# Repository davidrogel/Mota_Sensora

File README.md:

# Proyecto Mota Sensora

Proyecto para la creación de una Mota Sensora que permita leer los sensores acoplados.

### Dependencias ⚠️⚠️⚠️

La Mota depende del módulo que lee el sensor DHT11. Para descargar el proyecto junto a las dependencias usar:

```
git clone --recurse-submodules https://github.com/davidrogel/Mota_Sensora
```

## Sensores

| Sensor | Documentación |
|---|---|
| DHT11 | [Enlace](https://www.mouser.com/datasheet/2/758/DHT11-Technical-Data-Sheet-Translated-Version-1143054.pdf) |
| MQ-2 | [Enlace](http://gas-sensor.ru/pdf/combustible-gas-sensor.pdf) |
| MQ-3 | [Enlace](https://www.sparkfun.com/datasheets/Sensors/MQ-3.pdf) |

## Microcontrolador - ESP32

### Proyecto Base y otros

Se ha usado el proyecto de ejemplo **[ESP HTTP Client Example](https://github.com/espressif/esp-idf/tree/master/examples/protocols/esp_http_client)** como base para la creación del proyecto actual ya que ayuda a la hora de poder conectarse a una Wifi y trae ejemplos útiles de envio de datos a traves del protocolo HTTP.

A parte del proyecto mencionado antes, se ha usado el proyecto de ejemplo **[adc](https://github.com/espressif/esp-idf/tree/master/examples/peripherals/adc/single_read/adc)** para la lectura de valores analógicos

### Configuración y uso

Dentro de la carpeta del proyecto, configurar el tipo de dispositivo y abrir el **menuconfig** para configurar la ssid y password del WiFi y la api-key de thingspeak. También es posible modificar el pin digital del sensor DHT11.
```
idf.py set-target esp32
idf.py menuconfig
```

Tras configurar, hacer build y flashear el programa
```
idf.py build
idf.py -p PORT flash
```

El parámetro **PORT** será el USB que tengais conectado al dispositivo, en linux se puede hacer lo siguiente para buscar el USB:
```
ls /dev/ttyUSB*
```

Por último podeis monitorizar lo que está pasando (obtener los datos de salida por consola) usando monitor:
```
idf.py -p PORT monitor
```

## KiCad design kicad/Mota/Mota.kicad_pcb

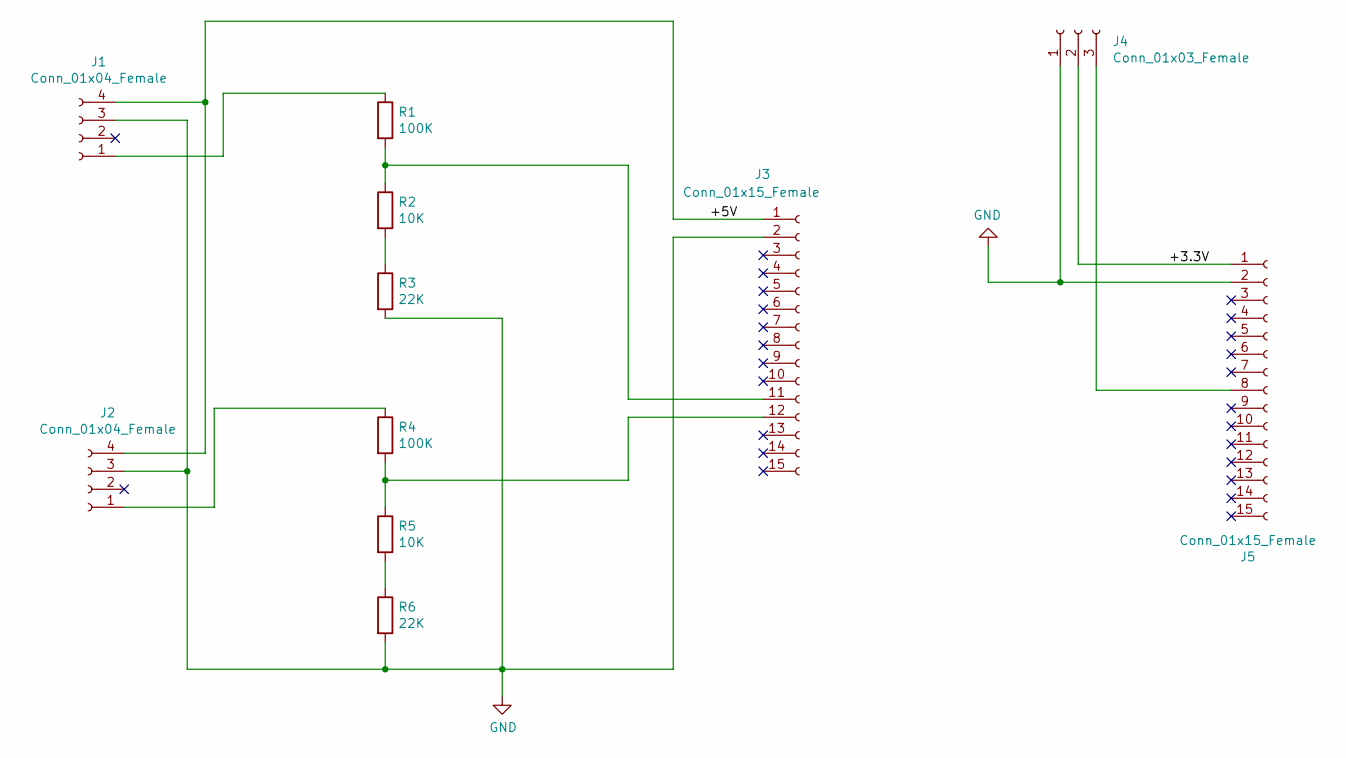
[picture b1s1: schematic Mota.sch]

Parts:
J1, J2: Conn_01x04_Female; PinSocket_1x04_P2.54mm_Vertical
J3, J5: Conn_01x15_Female; PinSocket_1x15_P2.54mm_Vertical
J4: Conn_01x03_Female; PinSocket_1x03_P2.54mm_Vertical
R1, R4: 100K; R_Axial_DIN0207_L6.3mm_D2.5mm_P2.54mm_Vertical
R2, R5: 10K; R_Axial_DIN0207_L6.3mm_D2.5mm_P2.54mm_Vertical
R3, R6: 22K; R_Axial_DIN0207_L6.3mm_D2.5mm_P2.54mm_Vertical

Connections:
/+3.3V: J4.2, J5.1
/+5V: J1.4, J2.4, J3.1
GND: J1.3, J2.3, J3.2, J4.1, J5.2, R3.2, R6.2
unnamed: J1.1, R1.1
unnamed: J2.1, R4.1
unnamed: J3.11, R1.2, R2.1
unnamed: J3.12, R4.2, R5.1
unnamed: J4.3, J5.8
unnamed: R2.2, R3.1
unnamed: R5.2, R6.1

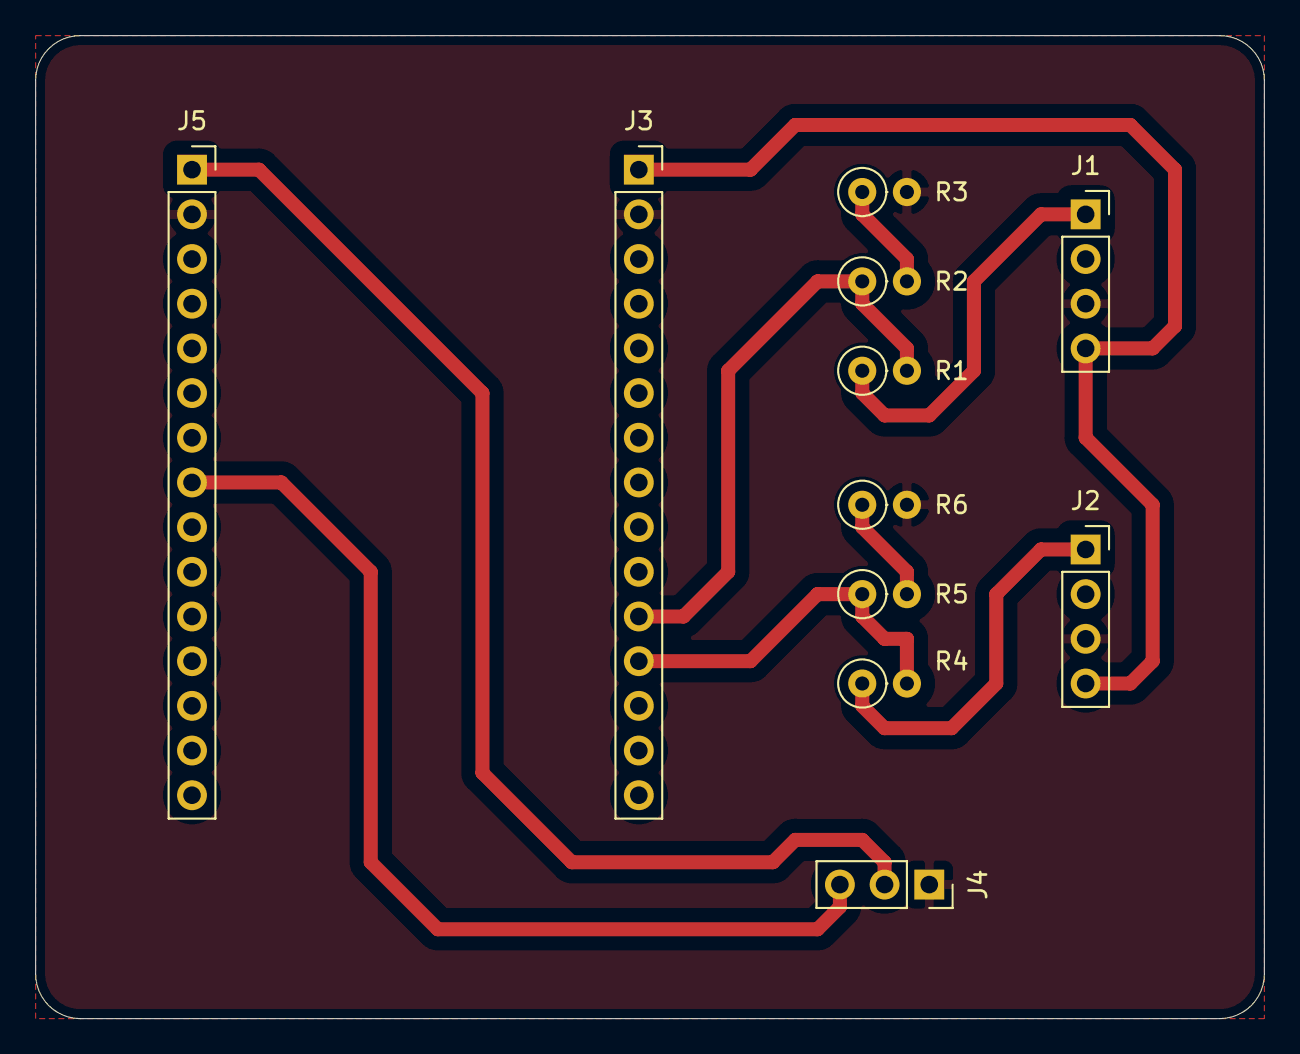
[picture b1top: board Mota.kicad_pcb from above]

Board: 2 copper layers, 69.9 x 55.9 mm, 11 parts (0 on the bottom side), 10 nets.

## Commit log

2022-04-26 Added gitignire and README
2022-04-26 added config for build process and cmake added source main.c
2022-04-26 added "project build" file where you can define values that can be readed in the sources files
2022-04-26 modified name in LICENSE
2022-04-26 config variable not need the CONFIG_ prefix, the builder adds it
2022-04-26 added component for the DHT11 sensor
2022-04-26 updated dht11 component
2022-04-26 added API_KEY as variable in the projbuild config file
2022-04-26 commenting and organizing the code
2022-04-26 gitmodules for DHT11
2022-04-27 added LICENSE to the top of the file, configured MQ2 and MQ3 sensors
2022-04-28 replaced hardcoded api-key with the config value updated readme
2022-06-10 kicad files
2022-06-20 new track sizes
